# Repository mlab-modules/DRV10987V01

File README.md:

# DRV10987V01 BLDC motor controller
This MLAB module features the [DRV10987](https://www.ti.com/lit/ds/symlink/drv10987.pdf?ts=1618316091180&ref_url=https%253A%252F%252Fwww.ti.com%252Fproduct%252FDRV10987) controller by Texas Instruments, designed for sensorless operation of Brushless DC ([BLDC](https://en.wikipedia.org/wiki/Brushless_DC_electric_motor)) and Permanent Magnet Synchronous Motors ([PMSM](https://en.wikipedia.org/wiki/Synchronous_motor#Permanent-magnet)).

### Description
The DRV10987 is a three-phase, sensorless, brushless DC motor driver that carries out all necessary functions for ordinary operation of brushless motors. It is a powerful solution that is compact and easy to implement.

This module offers a straightforward way to integrate this potent driver into your project, whether you're a hobbyist, a researcher, or a professional engineer.
Specifications

 *   Power supply ranging from 6.2V to 28V for driving motors with diverse voltage requirements
 *   Provide a continuous current of 2A and peak current of 3A
 *   Can control motor speed based on PWM, analogue, or digital (I2C) input
 *   Contains an FG pin that can be used to monitor motor rotation
 *   Integrated Buck converter at 5V and 100mA for powering peripheral devices
 *   Brushless design that minimizes wear and enables quiet operation
 *   Sensorless commutation for easy installation and maintenance
 *   PWM input frequency up to 100kHz
 *   Communication via I2C interface
 *   Built-in functions for overload and overheat protection

### Applications

This MLAB module equipted with the DRV10987 controller is highly versatile and is ideal for several applications where efficient and reliable control of smaller motors is required. Some of the primary use cases include:

 * **Small Drones and RC Models**: Due to its compact size and efficient operation, the DRV10987 controller is commonly used in the design of smaller drones and radio-controlled models. These vehicles require precise, reliable motor control for stabilization and maneuverability, which this module can adequately provide.
 * **Robotic Systems**: In robotics, precise control of motor speed and direction is essential. The DRV10987 controller's ability to regulate speed based on PWM, analogue, or digital (I2C) input makes it suitable for smaller robotic applications, including hobbyist robots, robotic toys, and educational kits.
 * **Home Appliances**: Small electrical appliances, such as desk fans, can make use of the DRV10987 controller for efficient and quiet operation. The controller's brushless design minimizes wear, which enhances the lifespan and user experience of these devices.
 * **Hobby Projects**: For hobbyists and DIY enthusiasts, this module with the DRV10987 controller is a great tool for various projects requiring control of smaller BLDC or PMSM motors. Its ease of use and versatility make it a valuable component in prototyping and experimentation.

### Installation and Integration
Our MLAB modules are designed to be as straightforward as possible for integration into your project. To connect this module, you only need a standard power supply and an I2C bus for communication with the control system.

### DRV10987

The DRV10987 from Texas Instruments is a three-phase, sensorless motor driver engineered for brushless DC (BLDC) and Permanent Magnet Synchronous Motors (PMSM). It is designed to handle all necessary functions for the routine operation of brushless motors. Capable of delivering a continuous current of 2A and a peak current of 3A, the DRV10987 can control motor speed based on PWM, analogue, or digital (I2C) input. This versatile chip also features an FG pin for monitoring motor rotation and has an integrated Buck converter at 5V and 100mA for powering peripheral devices. With built-in functions for overload and overheat protection, the DRV10987 represents a robust, compact, and efficient solution for a range of applications that require reliable motor control.

Detailed technical information about the DRV10987 controller can be found in the datasheet, available on the manufacturer's website [here](https://www.ti.com/lit/ds/symlink/drv10987.pdf?ts=1618316091180&ref_url=https%253A%252F%252Fwww.ti.com%252Fproduct%252FDRV10987).

### Schematics

## Availability and Pricing

The MLAB module DRV10987V01 with the DRV10987 controller is commercially produced and sold by Universal [Scientific Technologies s.r.o](https://ust.cz/). For information on availability and pricing, please contact the company directly via email at [info@ust.cz](mailto:info@ust.cz). They will be able to provide the most accurate and up-to-date information regarding your purchase inquiries.

### Conclusion
Regardless of whether you're building a sophisticated robotic system or a simple hobbyist project, this module with the DRV10987 controller from Texas Instruments is a powerful tool for sensorless control of BLDC and PMSM motors.

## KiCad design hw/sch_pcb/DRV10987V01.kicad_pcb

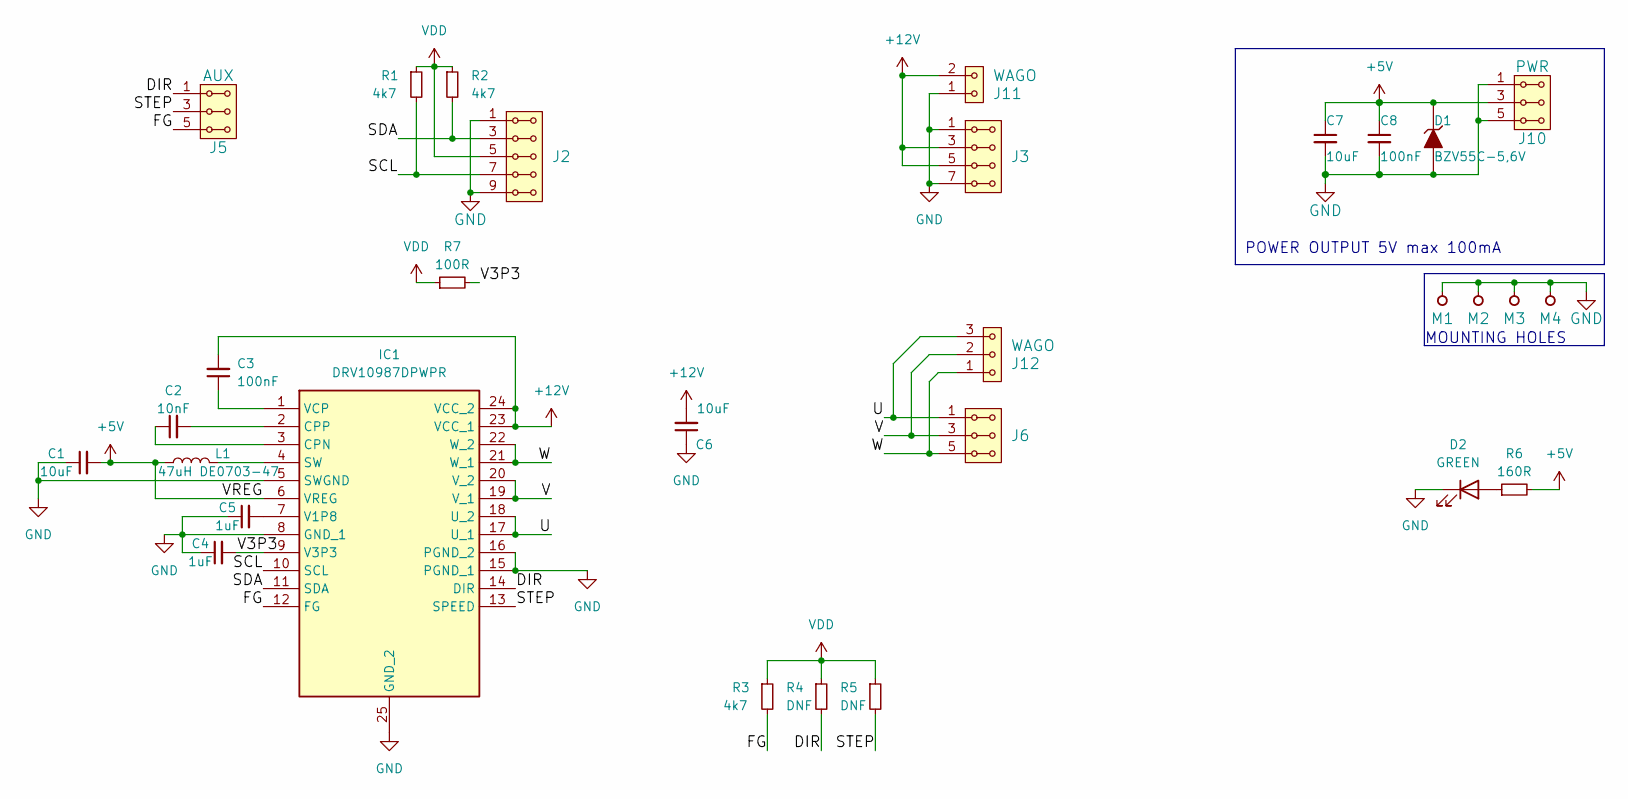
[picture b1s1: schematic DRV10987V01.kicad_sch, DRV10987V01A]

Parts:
C1, C6, C7: 10uF; C_0805_2012Metric
C2: 10nF; C_0805_2012Metric
C3, C8: 100nF; C_0805_2012Metric
C4, C5: 1uF; C_0805_2012Metric
D1: BZV55C-5,6V; D_SMA
D2: GREEN; LED_1206_2
IC1: DRV10987DPWPR; TSSOP-24_4.4x7.8mm_P0.65mm_PowerPAD; Manufacturer_Part_Number DRV10987DPWPR; Mouser Part Number 595-DRV10987DPWPR
J2: I2C; Straight_2x05
J3: HEADER_2x04_PARALLEL; Straight_2x04
J5: AUX; Straight_2x03
J6: MOTOR; Straight_2x03
J10: PWR; Straight_2x03
J11: WAGO; TerminalBlock_WAGO_236-102_1x02_P5.00mm_45Degree
J12: WAGO; TerminalBlock_WAGO_236-103_1x03_P5.00mm_45Degree
L1: 47uH DE0703-47; L_Ferrocore_DLG-0703; Manufacturer_Part_Number DE0703-47
M1, M2, M3, M4: HOLE M3; MountingHole_3mm
R1, R2, R3: 4k7; R_0805_2012Metric
R4, R5: DNF; R_0805_2012Metric
R6: 160R; R_0805_2012Metric
R7: 100R; R_0805_2012Metric

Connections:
+5V: C1.2, C7.1, C8.1, D1.1 (K), IC1.6 (VREG), J10.3, J10.4, L1.1, R6.2
+12V: C3.2, C6.2, IC1.23 (VCC_1), IC1.24 (VCC_2), J3.3, J3.4, J3.5, J3.6, J11.2
/DIR: IC1.14 (DIR), J5.1, J5.2, R4.2
/FG: IC1.12 (FG), J5.5, J5.6, R3.2
/SCL: IC1.10 (SCL), J2.7, J2.8, R1.2
/SDA: IC1.11 (SDA), J2.3, J2.4, R2.2
/STEP: IC1.13 (SPEED), J5.3, J5.4, R5.2
/U: IC1.17 (U_1), IC1.18 (U_2), J6.1, J6.2, J12.3
/V: IC1.19 (V_1), IC1.20 (V_2), J6.3, J6.4, J12.2
/V3P3: C4.2, IC1.9 (V3P3), R7.2
/W: IC1.21 (W_1), IC1.22 (W_2), J6.5, J6.6, J12.1
GND: C1.1, C4.1, C5.1, C6.1, C7.2, C8.2, D1.2 (A), D2.1 (K), IC1.5 (SWGND), IC1.8 (GND_1), IC1.15 (PGND_1), IC1.16 (PGND_2), IC1.25 (GND_2), J2.1, J2.2, J2.9, J2.10, J3.1, J3.2, J3.7, J3.8, J10.1, J10.2, J10.5, J10.6, J11.1, M1.1, M2.1, M3.1, M4.1
unnamed: D2.2 (A), R6.1
unnamed: C2.1, IC1.3 (CPN)
unnamed: C2.2, IC1.2 (CPP)
unnamed: IC1.4 (SW), L1.2
unnamed: C5.2, IC1.7 (V1P8)
unnamed: C3.1, IC1.1 (VCP)
VDD: J2.5, J2.6, R1.1, R2.1, R3.1, R4.1, R5.1, R7.1

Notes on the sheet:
POWER OUTPUT 5V max 100mA
MOUNTING HOLES

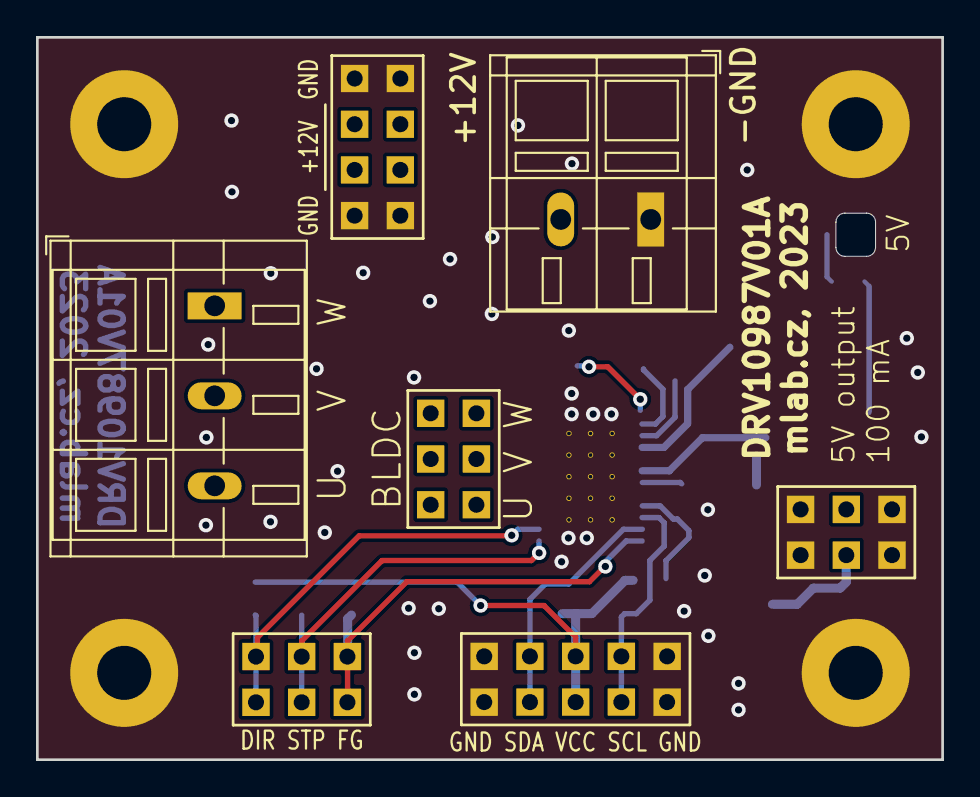
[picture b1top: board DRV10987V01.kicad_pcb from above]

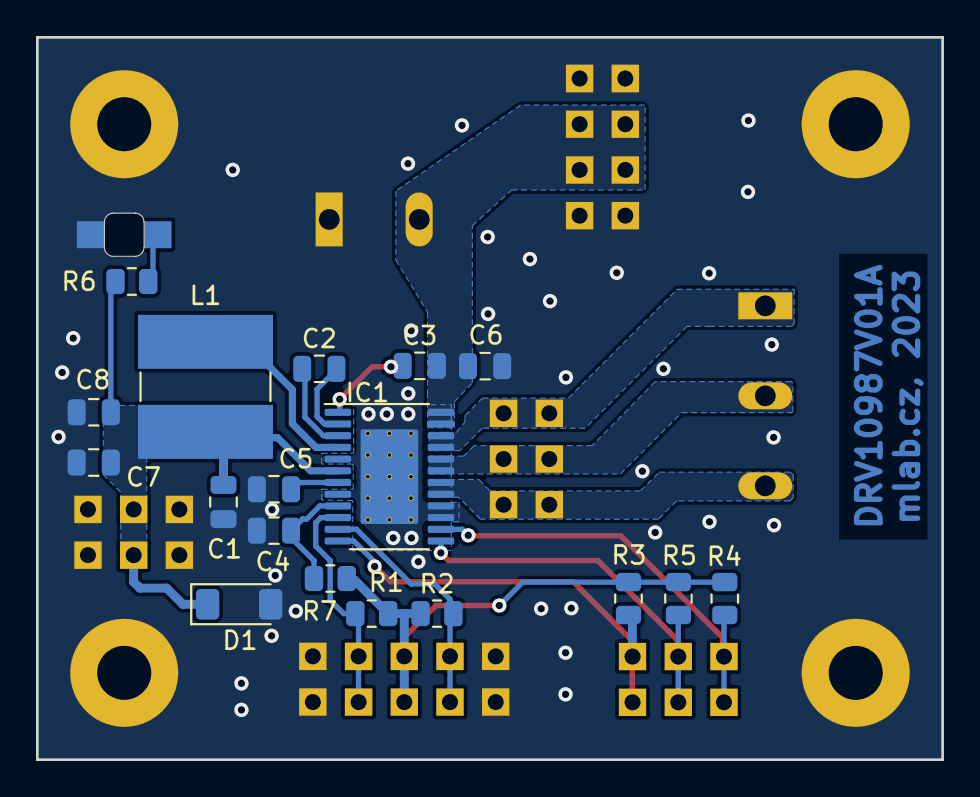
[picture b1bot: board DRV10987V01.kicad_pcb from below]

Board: 2 copper layers, 50.3 x 40.1 mm, 30 parts (19 on the bottom side), 19 nets.

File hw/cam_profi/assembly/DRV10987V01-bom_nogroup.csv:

Component,Description,Part,References,Value,Footprint,Quantity Per PCB,Datasheet,ust_id,arrow part number,arrow price/stock,height,manufacturer_name,manufacturer_part_number,mouser part number,mouser price/stock
1,"Unpolarized capacitor, small symbol",C_Small,C2,10nF,C_0805_2012Metric,1,~,5c70984712875079b91f8b49,,,,,,,
2,"Unpolarized capacitor, small symbol",C_Small,C3,100nF,C_0805_2012Metric,1,~,5c70984712875079b91f8b4c,,,,,,,
3,,C_Small-Device-ISM02A-rescue,C8,100nF,C_0805_2012Metric,1,,5c70984712875079b91f8b4c,,,,,,,
4,"Unpolarized capacitor, small symbol",C_Small,C4C5,1uF,C_0805_2012Metric,2,~,5c70984712875079b91f8b50,,,,,,,
5,"Unpolarized capacitor, small symbol",C_Small,C1C6,10uF,C_0805_2012Metric,2,~,5c70984712875079b91f8b53,,,,,,,
6,,C_Small-Device-ISM02A-rescue,C7,10uF,C_0805_2012Metric,1,,5c70984712875079b91f8b53,,,,,,,
7,,D_ZENER-MLAB_D,D1,"BZV55C-5,6V",D_SMA,1,,5c70984512875079b91f88b2,,,,,,,
8,Light emitting diode,LED,D2,GREEN,LED_1206_2,1,~,5c70984412875079b91f8895,,,,,,,
9,"12-V, 3-Phase, Sensorless BLDC Motor Controller",DRV10975PWPR,IC1,DRV10987DPWPR,TSSOP-24_4.4x7.8mm_P0.65mm_PowerPAD,1,https://www.ti.com/lit/ds/symlink/drv10975.pdf?ts=1619503349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,649ebe2a76c82a1d3b578220,DRV10975PWPR,https://www.arrow.com/en/products/drv10975pwpr/texas-instrum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,1.2,Texas Instruments,DRV10987DPWPR,595-DRV10987DPWPR,https://www.mouser.co.uk/ProductDetail/Texas-Instruments/DRV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
10,"2x03 2.54 mm pitch header, 2 pins next to each other are connected",HEADER_2x03_PARALLEL,J5,AUX,Straight_2x03,1,,,,,,,,,
11,"2x04 2.54 mm pitch header, 2 pins next to each other are connected",HEADER_2x04_PARALLEL,J3,HEADER_2x04_PARALLEL,Straight_2x04,1,,,,,,,,,
12,"2x05 2.54 mm pitch header, 2 pins next to each other are connected",HEADER_2x05_PARALLEL,J2,I2C,Straight_2x05,1,,,,,,,,,
13,"2x03 2.54 mm pitch header, 2 pins next to each other are connected",HEADER_2x03_PARALLEL,J6,MOTOR,Straight_2x03,1,,,,,,,,,
14,"2x03 2.54 mm pitch header, 2 pins next to each other are connected",HEADER_2x03_PARALLEL,J10,PWR,Straight_2x03,1,,,,,,,,,
15,1x02 2.54 mm pitch header,HEADER_1x02,J11,WAGO,TerminalBlock_WAGO_236-102_1x02_P5.00mm_45Degree,1,,,,,,,,,
16,1x03 2.54 mm pitch header,HEADER_1x03,J12,WAGO,TerminalBlock_WAGO_236-103_1x03_P5.00mm_45Degree,1,,,,,,,,,
17,Inductor,L,L1,47uH DE0703-47,L_Ferrocore_DLG-0703,1,~,5c70984712875079b91f8b69,,,,,DE0703-47,,
18,"Resistor, small symbol",R_Small,R7,100R,R_0805_2012Metric,1,~,5c70984512875079b91f8977,,,,,,,
19,"Resistor, small symbol",R_Small,R6,160R,R_0805_2012Metric,1,~,5c70984512875079b91f897b,,,,,,,
20,"Resistor, small symbol",R_Small,R1R2R3,4k7,R_0805_2012Metric,3,~,5c70984612875079b91f8995,,,,,,,

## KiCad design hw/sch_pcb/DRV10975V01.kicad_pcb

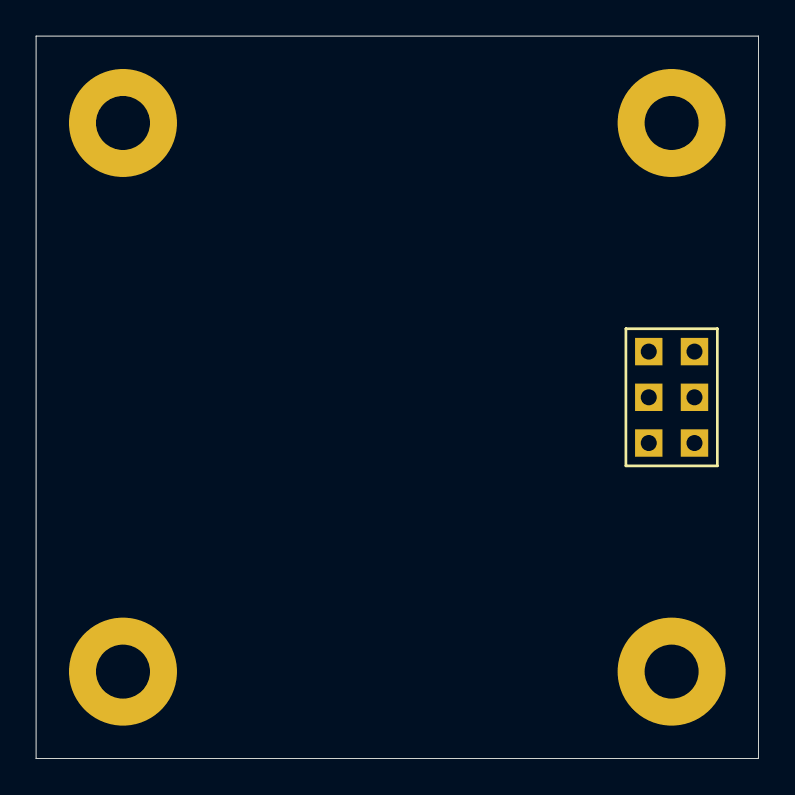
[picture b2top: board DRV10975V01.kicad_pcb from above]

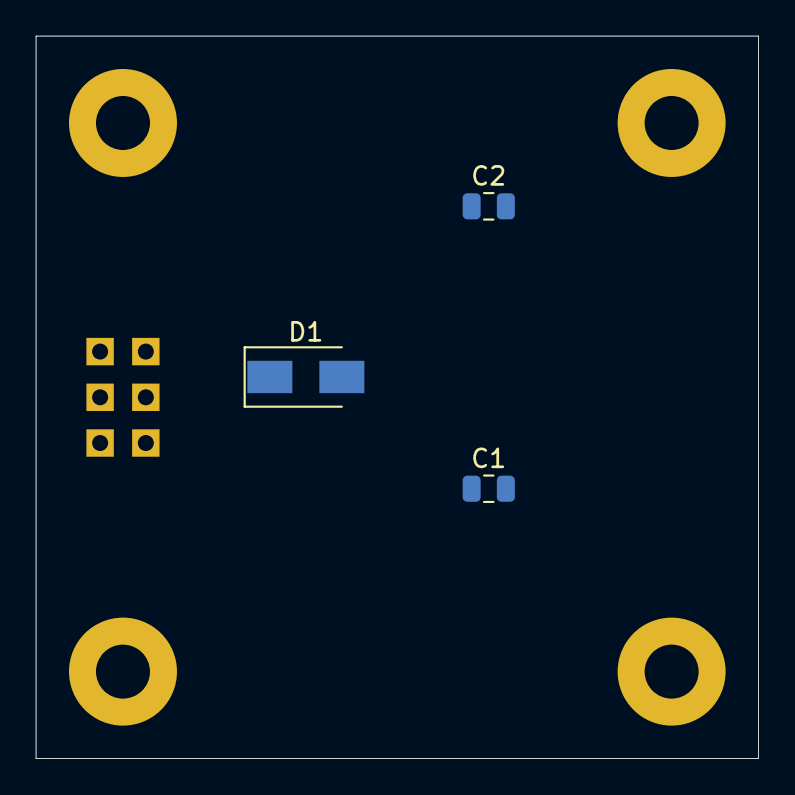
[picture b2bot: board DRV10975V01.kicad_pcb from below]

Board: 2 copper layers, 40.1 x 40.1 mm, 8 parts (3 on the bottom side), 2 nets, no tracks yet.

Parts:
C1: 10uF; C_0805_2012Metric
C2: 100nF; C_0805_2012Metric
D1: BZV55C-5,6V; D_SMA
J1: Umin ... Umax; Straight_2x03
M1, M2: HOLE M3; MountingHole_3mm
M3, M4: HOLE; MountingHole_3mm

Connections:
+5V: C1.1, C2.1, D1.1 (K), J1.3, J1.4
GND: C1.2, C2.2, D1.2 (A), J1.1, J1.2, J1.5, J1.6, M1.1, M2.1, M3.1, M4.1

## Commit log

2023-06-30 add assets, actions
2023-06-30 Update metadata files
2023-06-30 schematics and layout improvements
2023-06-30 Update actions products
2023-06-30 update silkscreen, add 5v indicator
2023-06-30 Zmena strany sroubu
2023-06-30 uprava napajeni 3v3
2023-06-30 repair silkscreen
2023-06-30 Edit PCB and schema
2023-07-04 Editing component values
2023-07-04 Editing B.FAB
2023-07-04 automated commit; add github actions
2023-07-05 Update workflow files
2023-07-11 pouze roztoceni a zastaveni na orevrcurrent
2023-07-11 exted
2023-07-11 prvni verze, kde se kontinuelne motor toci
2023-07-11 demo arduino
2023-07-11 arduino
2023-07-26 add notebook for Kt value determinating, add sample measurements of nanotec motors
2023-07-26 add DRV10987 control module
2023-07-26 clean repo
2023-07-26 update notebook
2023-09-16 Update status
